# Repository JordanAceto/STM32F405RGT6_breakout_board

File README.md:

# Breakout board for STM32F405

## The purpose of this project is primarily to test out pcb assembly by jlcpcb.

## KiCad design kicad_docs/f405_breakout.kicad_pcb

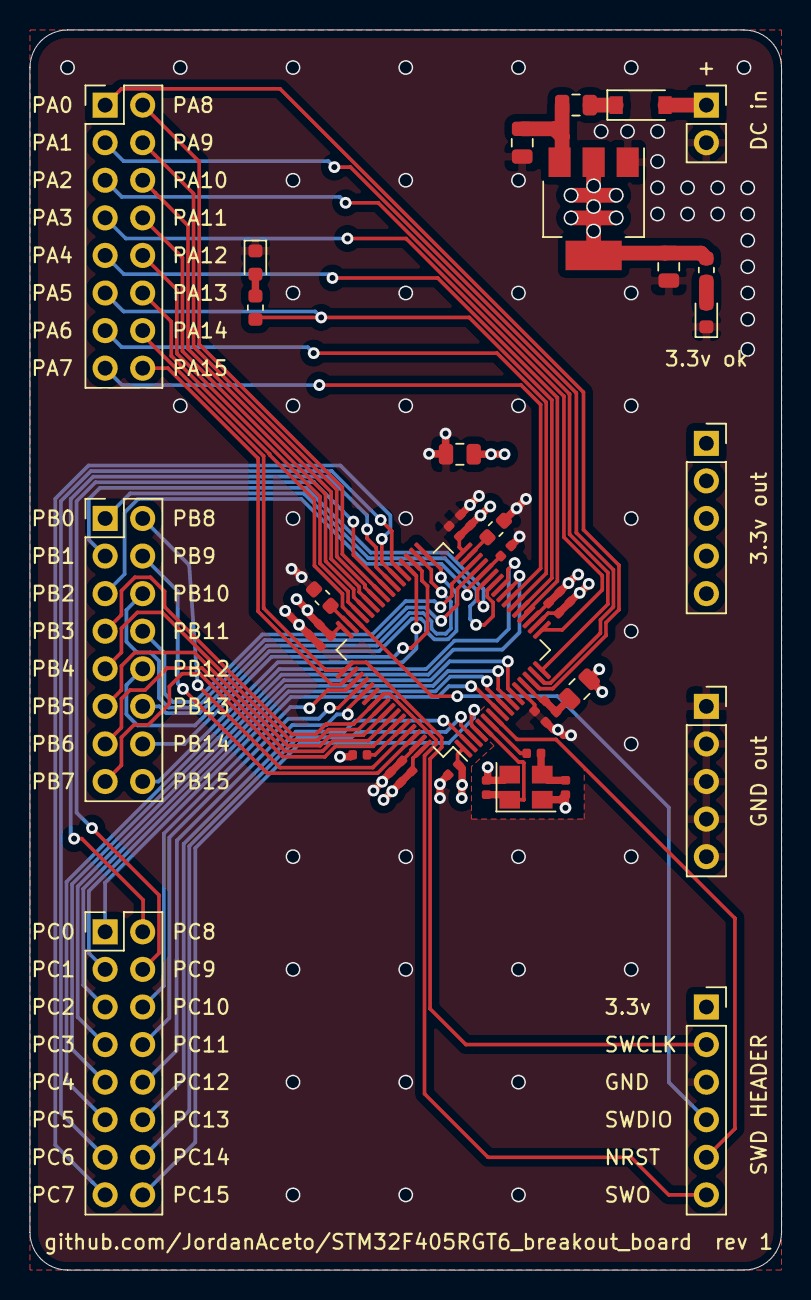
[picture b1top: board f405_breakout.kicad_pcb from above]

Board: 4 copper layers, 50.8 x 83.8 mm, 38 parts (0 on the bottom side), 63 nets.

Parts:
C1, C4, C8: 10uF; C_0805_2012Metric
C2, C3, C6, C7, C9, C10, C11, C12, C13, C14: 100nF; C_0402_1005Metric
C5: 10nF; C_0402_1005Metric
C15, C16: 2.2uF; C_0603_1608Metric
C17, C18: 12pF; C_0402_1005Metric
D1: B5819W; D_SOD-123
D2: power_LED; LED_0603_1608Metric
D3: user_LED; LED_0603_1608Metric
FB1, FB2: 100R @ 100MHz; L_0805_2012Metric
HSE1: 16MHz; Crystal_SMD_3225-4Pin_3.2x2.5mm
J1: DC_in; PinSocket_1x02_P2.54mm_Vertical
J2: SWD; PinSocket_1x06_P2.54mm_Vertical
J3: 3.3v_out; PinSocket_1x05_P2.54mm_Vertical
J4: gnd_out; PinSocket_1x05_P2.54mm_Vertical
J5: port_A; PinHeader_2x08_P2.54mm_Vertical
J6: port_B; PinHeader_2x08_P2.54mm_Vertical
J7: port_C; PinHeader_2x08_P2.54mm_Vertical
R1, R3: 2k2; R_0603_1608Metric
R2, R4: 10k; R_0402_1005Metric
R5: 100; R_0402_1005Metric
U1: AMS1117-3.3; SOT-223-3_TabPin2
U2: STM32F405RGT6; LQFP-64_10x10mm_P0.5mm

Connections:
+3.3VA: C2.1, C5.1, FB1.1, U2.13
+3V3: C1.1, C3.1, C6.1, C7.1, C8.1, C9.1, C10.1, C11.1, C12.1, C13.1, C14.1, FB1.2, J2.1, J3.1, J3.2, J3.3, J3.4, J3.5, R1.2, U1.2, U2.1, U2.19, U2.32, U2.48, U2.64
BOOT0: R2.2, U2.60
GND: C1.2, C2.2, C3.2, C4.2, C5.2, C6.2, C7.2, C8.2, C9.2, C10.2, C11.2, C12.2, C13.2, C14.2, C15.2, C16.2, C17.2, C18.2, D2.1, D3.1, HSE1.2, HSE1.4, J1.2, J2.3, J4.1, J4.2, J4.3, J4.4, J4.5, R2.1, R4.1, U1.1, U2.12, U2.18, U2.63
NRST: J2.5, U2.7
unnamed: C4.1, FB2.1, U1.3
unnamed: C15.1, U2.31
unnamed: C16.1, U2.47
unnamed: C18.1, HSE1.3, R5.2
unnamed: D1.1, FB2.2
unnamed: D2.2, R1.1
unnamed: D3.2, R3.1
PA0: J5.1, U2.14
PA1: J5.3, U2.15
PA2: J5.5, U2.16
PA3: J5.7, U2.17
PA4: J5.9, U2.20
PA5: J5.11, R3.2, U2.21
PA6: J5.13, U2.22
PA7: J5.15, U2.23
PA8: J5.2, U2.41
PA9: J5.4, U2.42
PA10: J5.6, U2.43
PA11: J5.8, U2.44
PA12: J5.10, U2.45
PA13_SWDIO: J2.4, J5.12, U2.46
PA14_SWCLK: J2.2, J5.14, U2.49
PA15: J5.16, U2.50
PB0: J6.1, U2.26
PB1: J6.3, U2.27
PB2_BOOT1: J6.5, R4.2, U2.28
PB3_SWO: J2.6, J6.7, U2.55
PB4: J6.9, U2.56
PB5: J6.11, U2.57
PB6: J6.13, U2.58
PB7: J6.15, U2.59
PB8: J6.2, U2.61
PB9: J6.4, U2.62
PB10: J6.6, U2.29
PB11: J6.8, U2.30
PB12: J6.10, U2.33
PB13: J6.12, U2.34
PB14: J6.14, U2.35
PB15: J6.16, U2.36
PC0: J7.1, U2.8
PC1: J7.3, U2.9
PC2: J7.5, U2.10
PC3: J7.7, U2.11
PC4: J7.9, U2.24
PC5: J7.11, U2.25
PC6: J7.13, U2.37
PC7: J7.15, U2.38
PC8: J7.2, U2.39
PC9: J7.4, U2.40
PC10: J7.6, U2.51
PC11: J7.8, U2.52
PC12: J7.10, U2.53
PC13: J7.12, U2.2
PC14: J7.14, U2.3
PC15: J7.16, U2.4
PH0: C17.1, HSE1.1, U2.5
PH1: R5.1, U2.6
VCC: D1.2, J1.1

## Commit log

2020-05-31 initial commit(2)
2020-05-31 add readme
2020-05-31 add git url to silkscreen
2020-05-31 create gerbers and assembly files
2020-05-31 add pcb pics
2020-05-31 fill in title blocks
2020-05-31 add pdf schematic
2020-05-31 add license
2020-06-02 fix gerber problem, add bottom mask
